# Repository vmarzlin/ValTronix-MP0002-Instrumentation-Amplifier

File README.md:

# MP0002 Instrumentation Amplifier
 ValTronix MP0002 Instrumentation Amplifier

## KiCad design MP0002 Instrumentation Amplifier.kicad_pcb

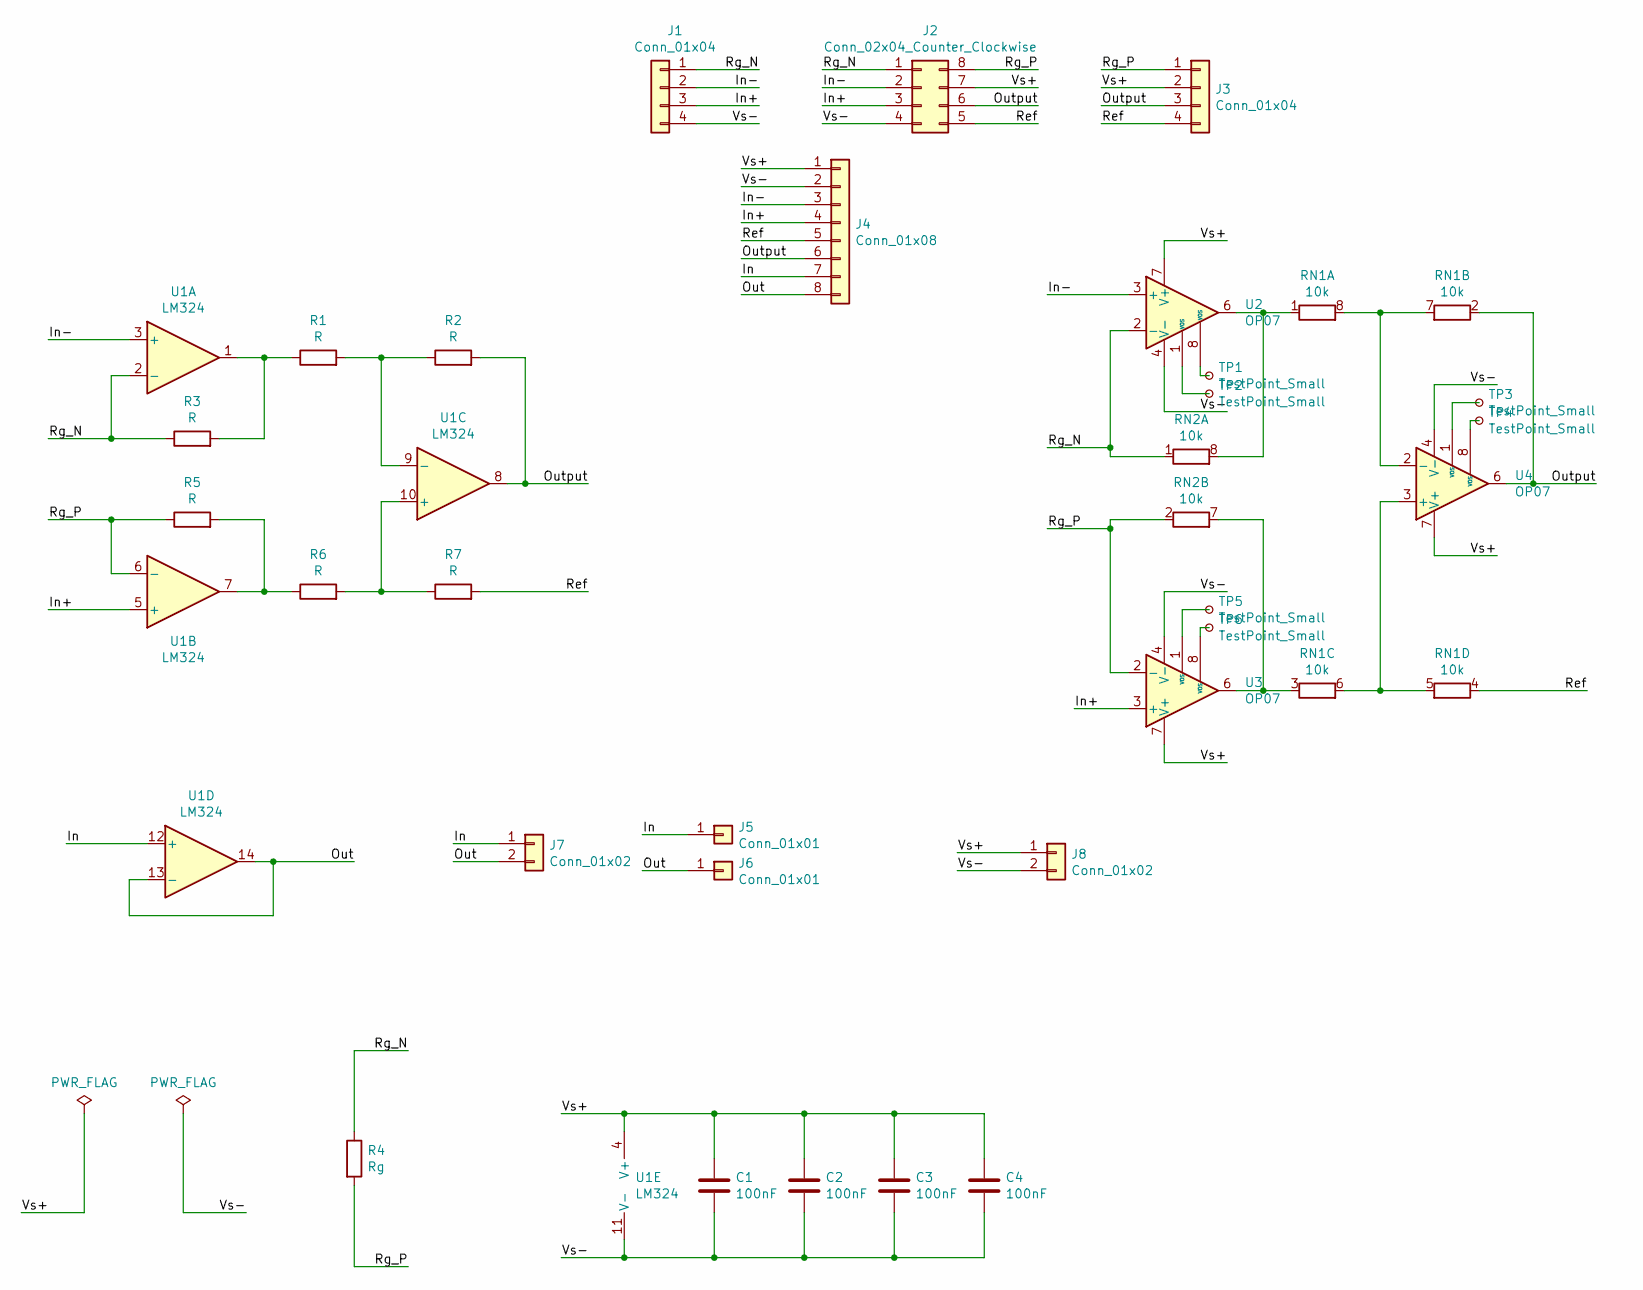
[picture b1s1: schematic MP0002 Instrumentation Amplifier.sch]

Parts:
C1, C2, C3, C4: 100nF; C_0603; LCSC Part# C14663
J1, J3: Conn_01x04; Pin_Header_Straight_1x04_Pitch2.54mm
J2: Conn_02x04_Counter_Clockwise; DIP-8_W7.62mm_LongPads
J4: Conn_01x08; Pin_Header_Angled_1x08_Pitch2.54mm
J5, J6: Conn_01x01; Pin_Header_Straight_1x01_Pitch2.54mm
J7, J8: Conn_01x02; Pin_Header_Straight_1x02_Pitch2.54mm
R1, R2, R3, R5, R6, R7: R; Resistor_SMD+THTuniversal_0805to1206_RM10_HandSoldering
R4: Rg; Resistor_SMD+THTuniversal_0805to1206_RM10_HandSoldering
RN1, RN2: 10k; R_Array_Concave_4x0603; LCSC Part# C29718
TP1, TP2, TP3, TP4, TP5, TP6: TestPoint_Small; Measurement_Point_Round-SMD-Pad_Big
U1: LM324; DIP-14_W7.62mm
U2, U3, U4: OP07; SOIC-8_3.9x4.9mm_Pitch1.27mm; LCSC Part# C7433

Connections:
/In: J4.7, J5.1, J7.1, U1.12 (+)
/In+: J1.3, J2.3, J4.4, U1.5 (+), U3.3 (+)
/In-: J1.2, J2.2, J4.3, U1.3 (+), U2.3 (+)
/Out: J4.8, J6.1, J7.2, U1.13 (-), U1.14
/Output: J2.6, J3.3, J4.6, R2.2, RN1.2 (R2.1), U1.8, U4.6
/Ref: J2.5, J3.4, J4.5, R7.2, RN1.4 (R4.1)
/Rg_N: J1.1, J2.1, R3.1, R4.1, RN2.1 (R1.1), U1.2 (-), U2.2 (-)
/Rg_P: J2.8, J3.1, R4.2, R5.1, RN2.2 (R2.1), U1.6 (-), U3.2 (-)
/Vs+: C1.1, C2.1, C3.1, C4.1, J2.7, J3.2, J4.1, J8.1, U1.4 (V+), U2.7 (V+), U3.7 (V+), U4.7 (V+)
/Vs-: C1.2, C2.2, C3.2, C4.2, J1.4, J2.4, J4.2, J8.2, U1.11 (V-), U2.4 (V-), U3.4 (V-), U4.4 (V-)
unnamed: R1.1, R3.2, U1.1
unnamed: R1.2, R2.1, U1.9 (-)
unnamed: R5.2, R6.1, U1.7
unnamed: R6.2, R7.1, U1.10 (+)
unnamed: RN1.1 (R1.1), RN2.8 (R1.2), U2.6
unnamed: RN1.3 (R3.1), RN2.7 (R2.2), U3.6
unnamed: RN1.5 (R4.2), RN1.6 (R3.2), U4.3 (+)
unnamed: RN1.7 (R2.2), RN1.8 (R1.2), U4.2 (-)
unnamed: TP1.1, U2.8 (VOS)
unnamed: TP2.1, U2.1 (VOS)
unnamed: TP3.1, U4.1 (VOS)
unnamed: TP4.1, U4.8 (VOS)
unnamed: TP5.1, U3.1 (VOS)
unnamed: TP6.1, U3.8 (VOS)

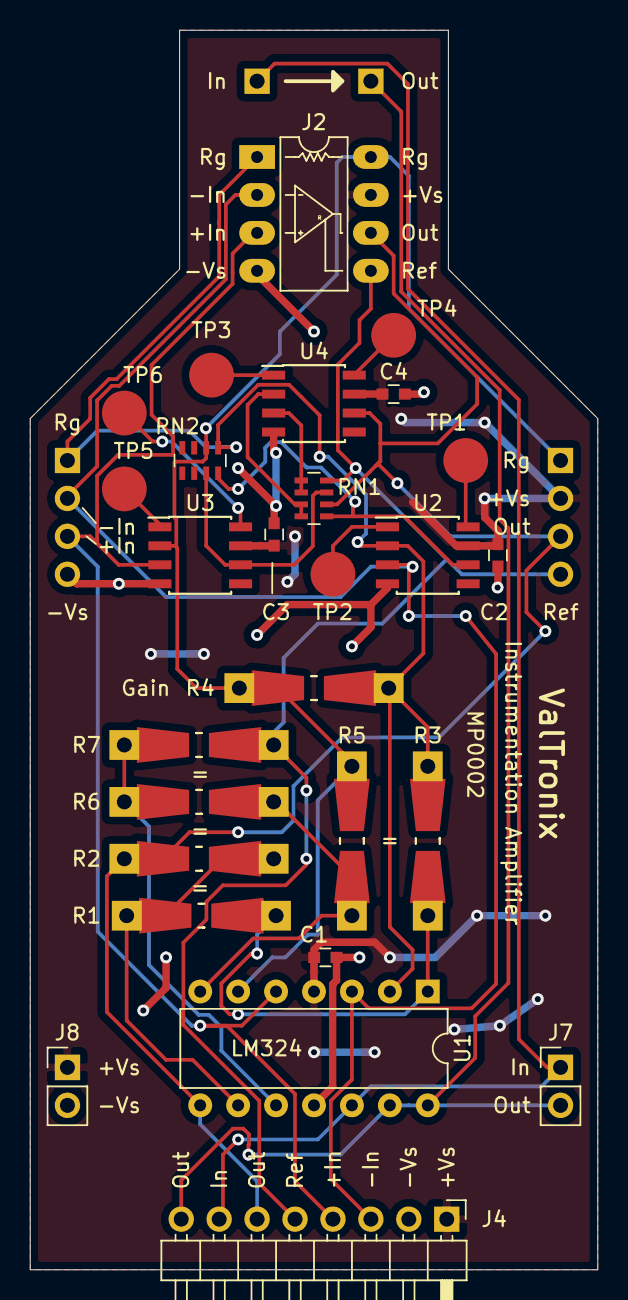
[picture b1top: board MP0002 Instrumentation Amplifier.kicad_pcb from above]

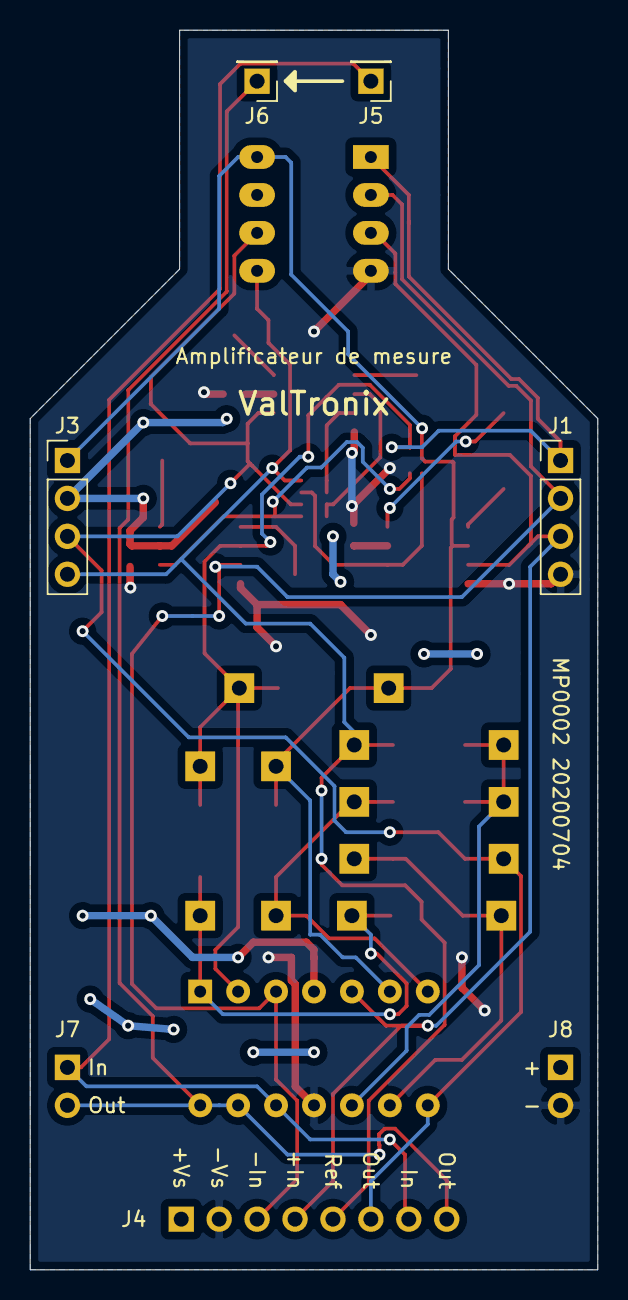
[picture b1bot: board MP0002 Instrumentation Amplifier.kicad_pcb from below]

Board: 2 copper layers, 38.0 x 83.0 mm, 31 parts (4 on the bottom side), 24 nets.

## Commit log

2020-07-04 Initial import
    Importing files
